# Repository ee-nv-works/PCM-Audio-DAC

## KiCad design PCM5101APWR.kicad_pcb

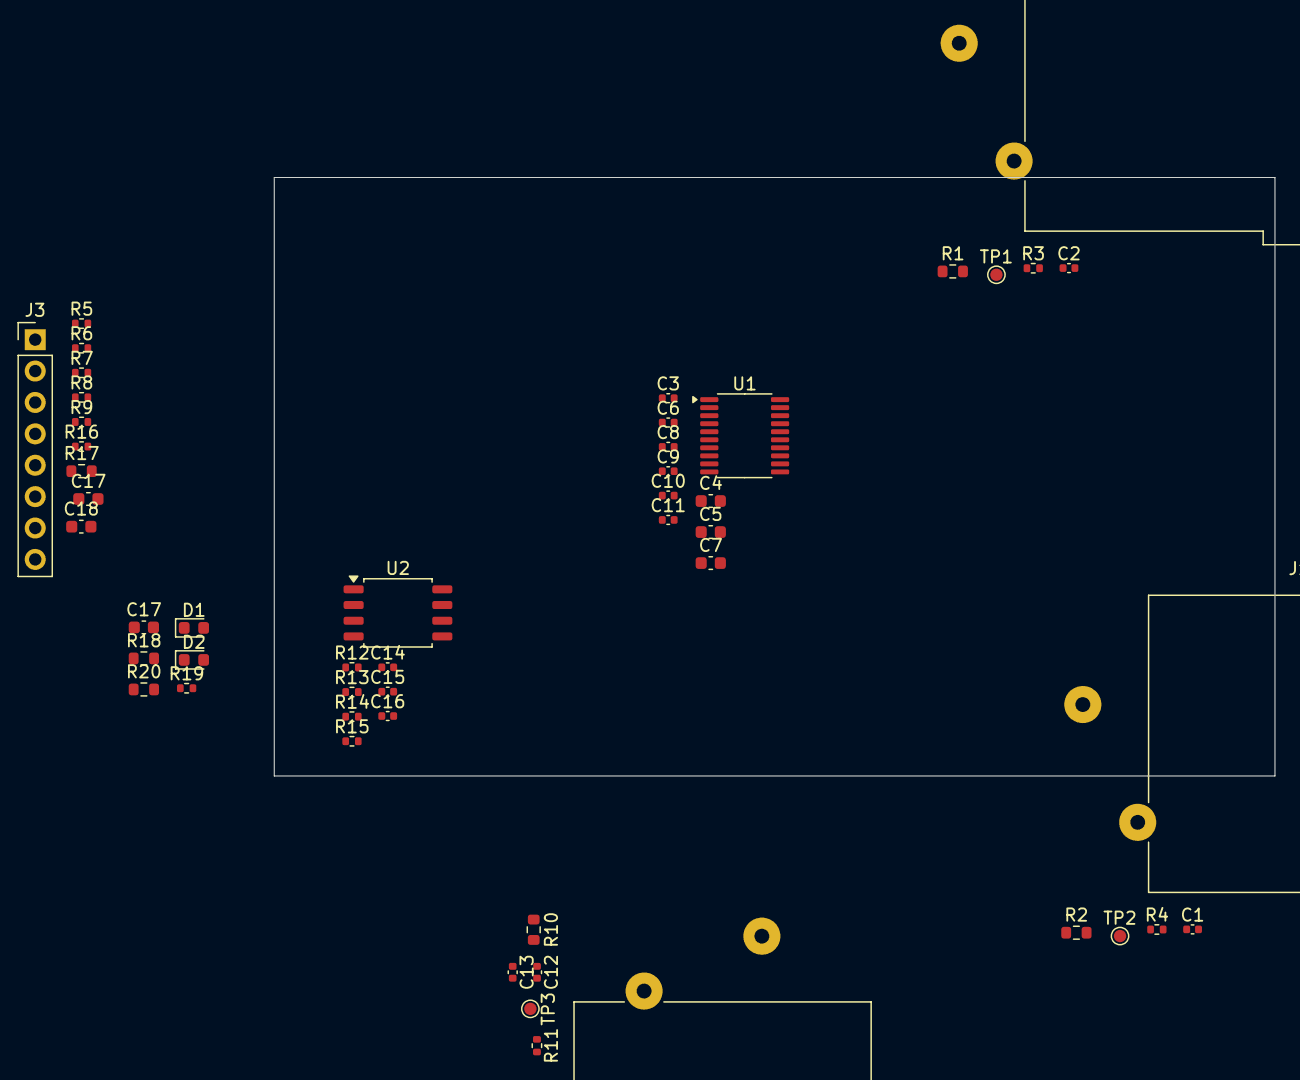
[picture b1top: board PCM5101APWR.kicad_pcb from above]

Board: 2 copper layers, 81.0 x 48.4 mm, 50 parts (0 on the bottom side), 28 nets, no tracks yet.

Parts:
C1, C2, C12, C13: 2.2n; C_0402_1005Metric
C3, C6, C8, C10, C14, C16: 100n; C_0402_1005Metric
C4, C5, C7, C17: 10u; C_0603_1608Metric
C9, C11, C15: 2.2u; C_0402_1005Metric
C17#2, C18: 100n; C_0603_1608Metric
D1, D2: LED; LED_0603_1608Metric
J1, J2, J4: AudioJack2; Jack_speakON-6.35mm_Neutrik_NLJ2MDXX-H_Horizontal
J3: Conn_01x08; PinHeader_1x08_P2.54mm_Vertical
R1, R2, R10, R18: 470; R_0603_1608Metric
R3, R4, R5, R6, R7, R8, R9, R11: 0; R_0402_1005Metric
R12, R13, R14, R15: 100k; R_0402_1005Metric
R16, R19: 1k; R_0402_1005Metric
R17: 100; R_0603_1608Metric
R20: 0; R_0603_1608Metric
TP1, TP2, TP3: TestPoint; TestPoint_Pad_D1.0mm
U1: PCM5101A; TSSOP-20_4.4x6.5mm_P0.65mm
U2: MCP6002-xSN; SOIC-8_5.3x5.3mm_P1.27mm

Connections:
+3.3V: C7.1, C8.1, C17.1, J3.1, R18.2, R19.2, R20.2, U1.17 (XSMT), U1.20 (DVDD)
+3.3VA: C3.1, C4.1, C5.1, C6.1, C16.2, C18.2, R13.2, R17.2, U1.1 (CPVDD), U1.8 (AVDD), U2.8 (V+)
/AUX_IN: C12.1, R10.2, TP3.1
/AUX_IN_MTCH: C13.1, C14.2, R10.1
/LRCK_CONN: J3.3, R5.1
/LRCK_IC: D1.1 (K), R5.2, U1.15 (LRCK)
GND: C1.2, C2.2, C3.2, C4.2, C5.2, C6.2, C7.2, C8.2, C10.2, C11.2, C12.2, C13.2, C15.2, C16.1, C17#2.1, C18.1, D2.1 (K), J3.2, J3.7, R3.1, R4.1, R8.1, R11.1, R12.1, R16.1, U1.3 (CPGND), U1.9 (AGND), U1.10 (DEMP), U1.11 (FLT), U1.16 (FMT), U1.19 (DGND), U2.4 (V-)
unnamed: C1.1, R2.2, TP2.1
unnamed: C2.1, R1.2, TP1.1
unnamed: C15.1, R15.1
unnamed: C17.2, C17#2.2, R16.2, R17.1, R20.1
unnamed: D1.2 (A), R18.1
unnamed: D2.2 (A), R19.1
unnamed: J3.4, R6.1
unnamed: J3.5, R7.1
unnamed: J3.6, R9.1
unnamed: J3.8, R14.2, U2.1
unnamed: R7.2, U1.13 (BCK)
unnamed: C9.2, U1.4 (CAPM)
unnamed: C9.1, U1.2 (CAPP)
unnamed: R6.2, U1.14 (DIN)
unnamed: C10.1, U1.18 (LDOO)
unnamed: R1.1, U1.6 (OUTL)
unnamed: R2.1, U1.7 (OUTR)
unnamed: R8.2, R9.2, U1.12 (SCK)
unnamed: C11.1, U1.5 (VNEG)
unnamed: C14.1, R12.2, R13.1, U2.3 (+)
unnamed: R14.1, R15.2, U2.2 (-)

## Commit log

2026-02-03 Create File
2026-02-03 test
2026-02-04 pushies
2026-02-15 Added more connectors
    Version change from 8 to 9
2026-02-15 eco'ed to pcb
2026-02-16 added buffer
2026-02-18 sch done. PCB started
